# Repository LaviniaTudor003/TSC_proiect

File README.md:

# e-book reader

# BOM (Bill Of Materials)

| Component                       | Supplier Link | Datasheet |
|--------------------------------|----------------|-----------|
| 744043680                     | [Model](https://ro.mouser.com/ProductDetail/Wurth-Elektronik/744043680?qs=PGXP4M47uW6VkZq%252BkzjrHA%3D%3D)   | [Datasheet](https://www.we-online.com/components/products/datasheet/744043680.pdf) |
| BD5229G-TR                    | [Model](https://www.digikey.ee/en/models/658502) | [Datasheet](https://www.rohm.com/datasheet?p=BD5229G&dist=Digi-key&media=referral&source=digi-key.com&campaign=Digi-key) |
| Capacitor 0402               | [Model](https://componentsearchengine.com/part-view/CC0402MRX5R5BB106/YAGEO) | [Datasheet](https://componentsearchengine.com/Datasheets/2/CC0402MRX5R5BB106.pdf) |
| CPH3225A                      | [Model](https://www.snapeda.com/parts/CPH3225A/Seiko+Instruments/view-part/?ref=eda)   | [Datasheet](https://www.snapeda.com/parts/CPH3225A/Seiko%20Instruments/datasheet/) |
| Custom Button                 | [Model](https://industry.panasonic.com/global/en/products/control/switch/light-touch/number/evqpuj02k) | [Datasheet](https://industry.panasonic.com/global/en/downloads?tab=catalog&small_g_cd=203&part_no=EVQPUJ02K) |
| MBR0530 Schottky Diode       | [Model](https://www.snapeda.com/parts/MBR0530/Onsemi/view-part/?ref=eda)                | [Datasheet](https://www.snapeda.com/parts/MBR0530/ON%20Semiconductor/datasheet/) |
| PGB1010603MR                 | [Model](https://www.snapeda.com/parts/PGB1010603MR/Littelfuse/view-part/?ref=eda)                | [Datasheet](https://www.snapeda.com/parts/PGB1010603MR/Littelfuse%20Inc./datasheet/) |
| QWIIC Connector              | [Model](https://www.snapeda.com/parts/PRT-14417/SparkFun/view-part/)                | [Datasheet](https://www.snapeda.com/parts/PRT-14417/SparkFun%20Electronics/datasheet/) |
| USB4110-GF-A                 | [Model](https://componentsearchengine.com/part-view/USB4110-GF-A/GCT%20(GLOBAL%20CONNECTOR%20TECHNOLOGY))                | [Datasheet](https://gct.co/files/drawings/usb4110.pdf) |
| USBLC6-2SC6Y                 | [Model](https://www.snapeda.com/parts/USBLC6-2SC6Y/STMicroelectronics/view-part/?ref=eda) | [Datasheet](https://www.snapeda.com/parts/USBLC6-2SC6Y/STMicroelectronics/datasheet/) |
| W25Q512JVEIQ                | [Model](https://www.digikey.ro/en/models/10244706)             | [Datasheet](https://www.winbond.com/resource-files/W25Q512JV%20SPI%20RevB%2006252019%20KMS.pdf) |
| RCL CPOL 3528                | [Model](https://www.snapeda.com/parts/TAJB475K025RNJ/AVX/view-part/?ref=dk&t=capacitor%203528&con_ref=None)                | [Datasheet](https://s3.amazonaws.com/snapeda/datasheet/TAJB475K025RNJ_AVX.pdf) |
| DS3231SN                      | [Model](https://www.snapeda.com/parts/DS3231SN%23/Analog+Devices/view-part/?ref=eda) | [Datasheet](https://www.snapeda.com/parts/DS3231SN%23/Analog%20Devices/datasheet/) |
| ESP32 WROVER 0805 Capacitor  | [Model](https://ro.mouser.com/ProductDetail/KYOCERA-AVX/SD0805S020S1R0?qs=jCA%252BPfw4LHbpkAoSnwrdjw%3D%3D)                | [Datasheet](https://ro.mouser.com/datasheet/2/40/schottky-3165252.pdf) |
| ESP32 WROVER BME680 Sensor   | [Model](https://www.digikey.ro/en/models/7401317)                | [Datasheet](https://www.bosch-sensortec.com/media/boschsensortec/downloads/datasheets/bst-bme680-ds001.pdf) |
| ESP32 WROVER MCP73831 Power Management | [Model](https://www.snapeda.com/parts/MCP73831T-2ACI/OT/Microchip/view-part/)         | [Datasheet](https://www.snapeda.com/parts/MCP73831T-2ACI/OT/Microchip/datasheet/) |
| ESP32C6 Varistor 1812        | [Model](https://www.snapeda.com/parts/RC0603JR-070RL/Yageo/view-part/)                | [Datasheet](https://www.snapeda.com/parts/RC0603JR-070RL/Yageo/datasheet/) |
| ESP32C6 WROOM-1-N8           | [Model](https://www.snapeda.com/parts/ESP32-C6-WROOM-1-N8/Espressif+Systems/view-part/?ref=eda)                | [Datasheet](https://www.snapeda.com/parts/ESP32-C6-WROOM-1-N8/Espressif%20Systems/datasheet/) |
| FH34SRJ-24S-0.5SH            | [Model](https://www.snapeda.com/parts/FH34SRJ-24S-0.5SH(99)/Hirose/view-part/)                | [Datasheet](https://www.snapeda.com/parts/FH34SRJ-24S-0.5SH(99)/Hirose%20Connector/datasheet/) |
| LED Chip 0603                | [Model](https://grabcad.com/library/0603-smd-led-1)                | [Datasheet](https://www.snapeda.com/parts/KP-1608SURCK/Kingbright/datasheet/) |
| MAX17048G+T10                | [Model](https://www.snapeda.com/parts/MAX17048G+T10/Analog+Devices/view-part/?ref=eda)                | [Datasheet](https://www.snapeda.com/parts/MAX17048G+T10/Analog%20Devices/datasheet/) |
| Resistor 0402                | [Model](https://componentsearchengine.com/part-view/R0402%201%25%20100%20K%20(RC0402FR-07100KL)/YAGEO)                | [Datasheet](https://www.yageo.com/upload/media/product/products/datasheet/rchip/PYu-RC_Group_51_RoHS_L_12.pdf) |
| 112A-TAAR-R03                  | [Model](https://www.snapeda.com/parts/112A-TAAR-R03/Attend/view-part/) | [Datasheet](https://www.snapeda.com/parts/112A-TAAR-R03/Attend/datasheet/) |
| SI1308EDL-T1-GE3 MOSFET      | [Model](https://www.snapeda.com/parts/SI1308EDL-T1-GE3/Vishay+Siliconix/view-part/?ref=eda)                | [Datasheet](https://www.snapeda.com/parts/SI1308EDL-T1-GE3/Vishay%20Siliconix/datasheet/) |
| SJ                           | [Model](https://grabcad.com/library/solder-jumpers-1)                | [Datasheet](https://github.com/TeodorStamatin/EBook_Reader/tree/main) |
| XC6220A331MR-G              | [Model](https://componentsearchengine.com/part-view/XC6220A331MR-G/Torex)             | [Datasheet](https://product.torexsemi.com/system/files/series/xc6220.pdf) |

# Conexiuni și module hardware utilizate:
•	USB-C Connector + ESD Protection
-	Intrare principală de alimentare și programare.
•	LDO Voltage Regulator
-	Reglează tensiunea de intrare la 3.3V stabil pentru alimentarea ESP32 și altor componente.
•	Li-Po Battery Charging Controller
-	Încarcă un acumulator Li-Po de la 5V (USB)
•	ESP32-C6
-	Microcontroller principal - responsabil de control, procesare si comunicare
•	E-Paper Drive Circuit
-	Oferă semnalul de putere necesar pentru activarea e-paper-ului
•	Display Type Selector
-	Permite comutarea
•	Voltage Supervisor + Reset
-	Asigură resetul corect la pornire
Poziționarea componentelor a fost gândită pentru:
•	acces facil la butoane,
•	vizibilitatea e-paper-ului,
•	montarea sigură a bateriei cu suport mecanic.
(pe baza schemei si recomandarilor primite)

# Functionalitate Hardware:
**Componente, Module și Senzori**
**Alimentare și Management Energie**
 Conector USB-C + Protecție ESD
 Funcție: Asigură alimentarea principală a sistemului și protejează împotriva descărcărilor electrostatice.
 
 Controler Încărcare Baterie – MCP73831
 Funcție: Gestionează încărcarea bateriei Li-Po, controlează curentul de încărcare.
 
 Baterie Li-Po
 Funcție: Sursă de alimentare secundară pentru funcționare autonomă (fără USB).
 
 Regulator de Tensiune LDO (3.3V)
 Funcție: Stabilizează tensiunea de alimentare pentru microcontroler și restul componentelor.
 
 Supervizor Tensiune + Buton Reset/Boot
 Funcție: Monitorizează nivelul tensiunii de alimentare și permite resetarea sau intrarea în modul boot al ESP32-C6.

**Control și Procesare:**
 ESP32-C6-WROOM-1-N8
 Funcție: Microcontroler principal. Gestionează comunicațiile (SPI, I2C, UART), interacțiunea cu senzorii și controlul perifericelor. Oferă conectivitate Wi-Fi și Bluetooth Low Energy.
 
 Memorie Externă NOR Flash – 64MB
 Funcție: Stocare extinsă pentru firmware și date.
 Interfață: SPI.

**Timp Real:**
 Modul RTC – DS3231SN
 Funcție: Ceas de timp real de înaltă precizie, cu suport pentru alarmă și funcționare pe baterie de backup.
 Interfață: I2C.

**Senzori de Mediu:**
 BME688 – Senzor ambiental
 Funcție: Măsoară temperatura, umiditatea, presiunea atmosferică și compușii organici volatili (VOC).
 Interfață: I2C (Qwiic / Stemma QT pentru conectare rapidă).
 Consum: Standby ultra-low power, activ ~3.1 mA.

**Afișaj:**
 Circuit de control pentru ecran E-Paper + Header de conectare
 Funcție: Generează semnalele necesare pentru funcționarea ecranelor E-Paper.
 Interfață: SPI cu linii de control dedicate (Busy, Reset, DC, CS).

**Stocare locală:**
 Slot Card microSD
 Funcție: Permite salvarea datelor local (loguri, configurări, fișiere).
 Interfață: SPI, cu semnal Chip Select dedicat.

**Interfețe de Comunicație:**
 I2C: Utilizat pentru BME688 și DS3231SN.
 SPI: Utilizat pentru NOR Flash, E-Paper Display și Card SD.
 UART: Disponibil pentru debug sau extensii opționale.
 Wi-Fi & Bluetooth LE: Oferite de modulul ESP32-C6.
# Pini ESP32-C6

| Componenta / Rol                             | Pin ESP32-C6     | Motivație                                           |
|---------------------------------------------|------------------|-----------------------------------------------------|
| I2C SDA către BME688 și DS3231SN             | IO14 (SDA)       | Transmite date între microcontroler și dispozitivele I2C. |
| I2C SCL către BME688 și DS3231SN             | IO15 (SCL)       | Coordonează sincronizarea comunicării I2C.          |
| SPI MOSI către NOR Flash, E-Paper, SD Card   | IO6 (MOSI)       | Trimite informații din ESP32 către perifericele conectate pe SPI. |
| SPI MISO din NOR Flash, E-Paper, SD Card     | IO7 (MISO)       | Primește date înapoi de la dispozitivele SPI.       |
| SPI Clock                                     | IO8 (SCK)        | Oferă impulsurile de sincronizare pentru magistrala SPI. |
| Chip Select NOR Flash                         | IO9 (CS1)        | Activează memoria NOR atunci când este utilizată.   |
| Chip Select E-Paper Display                   | IO10 (CS2)       | Selectează modulul de afișaj E-Paper pentru transmiterea de date. |
| Chip Select SD Card                           | IO11 (CS3)       | Indică faptul că SD Card-ul este dispozitivul activ pe SPI. |
| UART RX, TX (debug)                           | IO16, IO17       | Permite trimiterea și recepționarea datelor pentru depanare și upload firmware. |
| Reset / Boot control                          | IO21             | Folosit pentru repornirea manuală a sistemului sau inițierea modului de programare. |

# PCB_2D:

# PCB_3D:

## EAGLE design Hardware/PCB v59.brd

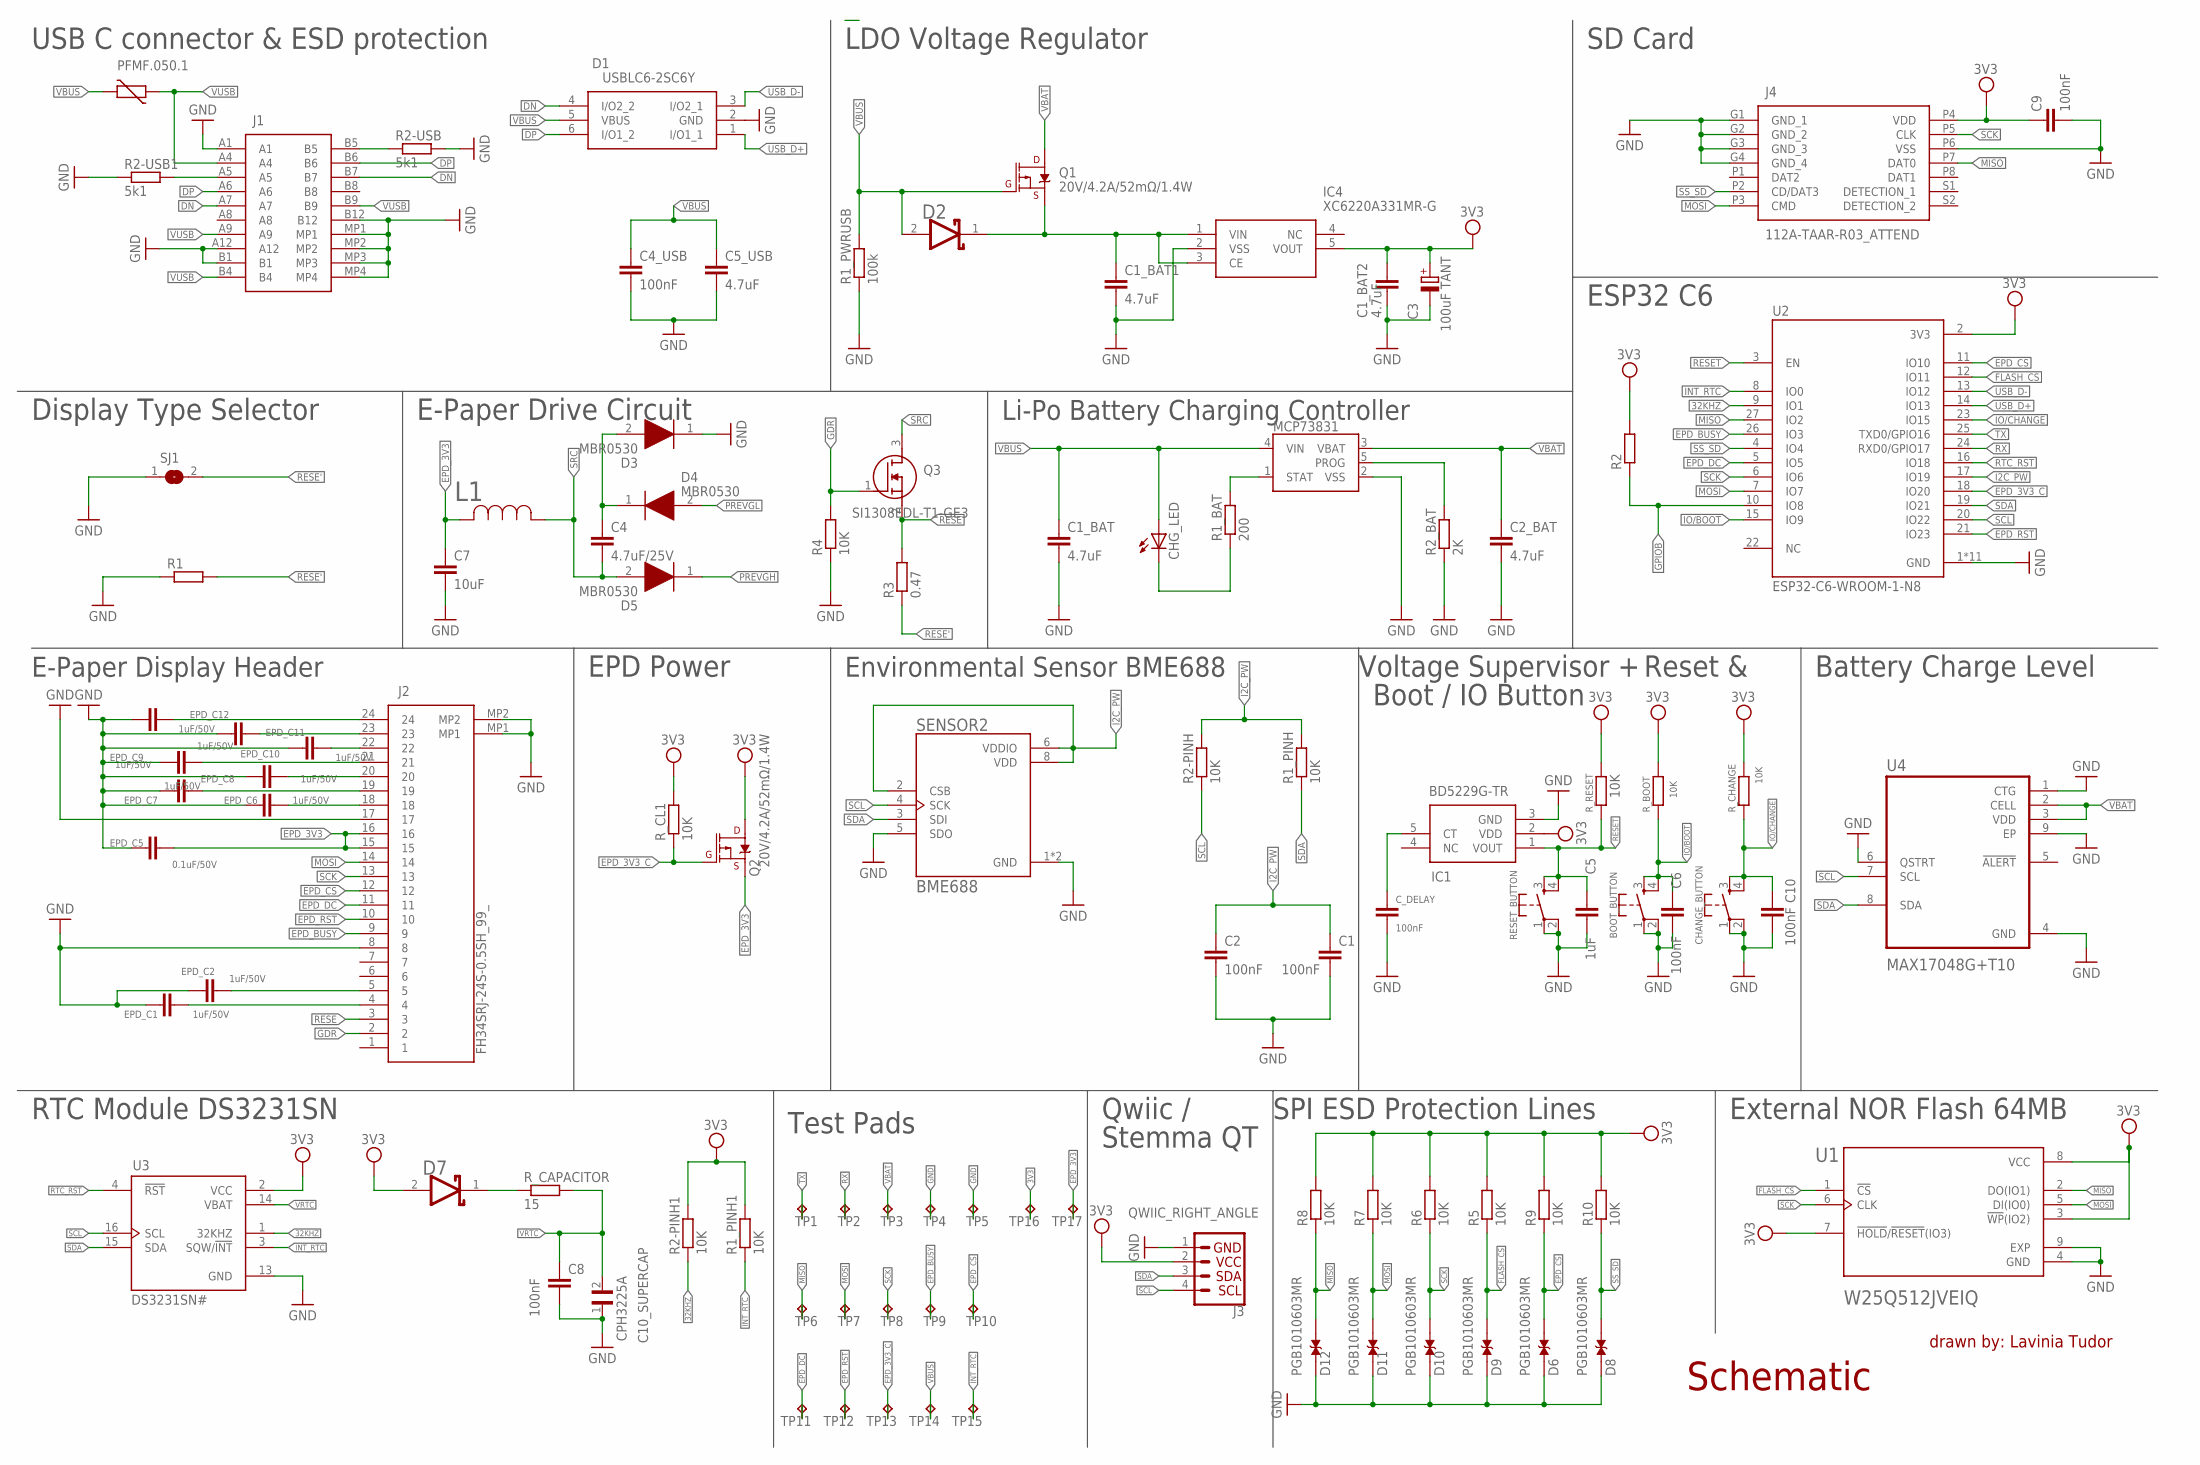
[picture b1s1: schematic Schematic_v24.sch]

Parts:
BOOT_BUTTON: BUTTON_CUSYOMV1; MYBUTTON
C1, C2, C6, C8, C10: 100nF; ESP32_WROVER_EAGLE-LTSPICE_C0402
C1_BAT, C1_BAT1, C1_BAT2, C2_BAT: 4.7uF; ESP32_WROVER_EAGLE-LTSPICE_C0402
C3: 100uF TANT; RCL_CT3528
C4: 4.7uF/25V; ESP32_WROVER_EAGLE-LTSPICE_C0402
C4_USB, C9: 100nF; EAGLE-LTSPICE_C0402
C5: 1uF; ESP32_WROVER_EAGLE-LTSPICE_C0402
C5_USB: 4.7uF; EAGLE-LTSPICE_C0402
C7: 10uF; ESP32_WROVER_EAGLE-LTSPICE_C0402
C10_SUPERCAP: CPH3225A; CAPCP3225X100N
CHANGE_BUTTON: BUTTON_CUSYOMV1; MYBUTTON
CHG_LED: ADAFRUIT_LEDCHIP-LED0603; ADAFRUIT_CHIP-LED0603
C_DELAY: 100nF; ESP32_WROVER_EAGLE-LTSPICE_C0402
D1: USBLC6-2SC6Y; SOT95P280X145-6N
D2, D7: ESP32_WROVER_AVX---SD0805S020S1R0_AVX_SD0805S020S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; ESP32_WROVER_AVX---SD0805S020S1R0_AVX_SD0805S020S1R0_0
D3, D4, D5: MBR0530; SOD3716X135N
D6, D8, D9, D10, D11, D12: PGB1010603MR; DIOC1608X36N
EPD_C1, EPD_C2, EPD_C6, EPD_C7, EPD_C8, EPD_C9, EPD_C10, EPD_C11, EPD_C12: 1uF/50V; ESP32_WROVER_EAGLE-LTSPICE_C0402
EPD_C5: 0.1uF/50V; ESP32_WROVER_EAGLE-LTSPICE_C0402
IC1: BD5229G-TR; SOT95P280X125-5N
IC4: XC6220A331MR-G; SOT95P280X120-5N
J1: SAMACSYS_PARTS_USB4110-GF-A; SAMACSYS_PARTS_USB4110GFA
J2: FH34SRJ-24S-0.5SH_99_; FH34SRJ24S05SH99
J3: QWIIC_RIGHT_ANGLE; JST04_1MM_RA
J4: 112A-TAAR-R03_ATTEND; 112ATAARR03ATTEND
L1: 744043680IND_4828-WE-TPC_WRE; IND_4828-WE-TPC_WRE
MCP73831: ESP32_WROVER_SPARKFUN-IC-POWER_MCP73831; ESP32_WROVER_SPARKFUN-IC-POWER_SOT23-5
PFMF.050.1: ESP32C6_VARISTORCN1812; ESP32C6_VARISTOR_CT/CN1812
Q1, Q2: 20V/4.2A/52mΩ/1.4W; ESP32_WROVER_SPARKFUN-DISCRETESEMI_SOT23-3
Q3: SI1308EDL-T1-GE3; SOT65P210X110-3N
R1, R2: ESP32_WROVER_EAGLE-LTSPICE_RR0402; ESP32_WROVER_EAGLE-LTSPICE_R0402
R1_BAT: 200; ESP32_WROVER_EAGLE-LTSPICE_R0402
R1_PINH, R1_PINH1, R2-PINH, R2-PINH1, R4, R5, R6, R7, R8, R9, R10: 10K; ESP32_WROVER_EAGLE-LTSPICE_R0402
R1_PWRUSB: 100k; ESP32_WROVER_EAGLE-LTSPICE_R0402
R2-USB, R2-USB1: 5k1; ESP32_WROVER_EAGLE-LTSPICE_R0402
R2_BAT: 2K; ESP32_WROVER_EAGLE-LTSPICE_R0402
R3: 0.47; ESP32_WROVER_EAGLE-LTSPICE_R0402
RESET_BUTTON: BUTTON_CUSYOMV1; MYBUTTON
R_BOOT: 10K; ESP32_WROVER_EAGLE-LTSPICE_R0402
R_CAPACITOR: 15; ESP32_WROVER_EAGLE-LTSPICE_R0402
R_CHANGE: 10K; ESP32_WROVER_EAGLE-LTSPICE_R0402
R_CL1: 10K; ESP32_WROVER_EAGLE-LTSPICE_R0402
R_RESET: 10K; ESP32_WROVER_EAGLE-LTSPICE_R0402
SENSOR2: BME688; ESP32_WROVER_BME680_PSON80P300X300X100-8N
SJ1: SJ
TP1, TP2, TP3, TP4, TP5, TP6, TP7, TP8, TP9, TP10, TP11, TP12, TP13, TP14, TP15, TP16, TP17: TPTP20R; TP20R
U1: W25Q512JVEIQ; SON127P600X800X80-9N
U2: ESP32-C6-WROOM-1-N8; XCVR_ESP32-C6-WROOM-1-N8
U3: DS3231SN#; SOIC127P1032X265-16N
U4: MAX17048G+T10; SON50P200X200X80-9N

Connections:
3V3: C1_BAT2.1, C3.+, C9.1, D7.2 (ANODE), IC1.2 (VDD), IC4.5 (VOUT), J3.2, J4.P4 (VDD), Q2.3 (D), R1_PINH1.2, R2.2, R2-PINH1.2, R5.2, R6.2, R7.2, R8.2, R9.2, R10.2, R_BOOT.2, R_CHANGE.2, R_CL1.2, R_RESET.2, TP16.TP, U1.3 (!WP!(IO2)), U1.7 (!HOLD!/!RESET!(IO3)), U1.8 (VCC), U2.2 (3V3), U3.2 (VCC)
32KHZ: R2-PINH1.1, U2.9 (IO1), U3.1 (32KHZ)
DN: D1.4 (I/O2_2), J1.A7, J1.B7
DP: D1.6 (I/O1_2), J1.A6, J1.B6
EPD_3V3: C7.1, EPD_C5.2, J2.15, J2.16, L1.2, Q2.2 (S), TP17.TP
EPD_3V3_C: Q2.1 (G), R_CL1.1, TP13.TP, U2.18 (IO20)
EPD_BUSY: J2.9, TP9.TP, U2.26 (IO3)
EPD_CS: D6.2, J2.12, R9.1, TP10.TP, U2.11 (IO10)
EPD_DC: J2.11, TP11.TP, U2.5 (IO5)
EPD_RST: J2.10, TP12.TP, U2.21 (IO23)
FLASH_CS: D9.2, R5.1, U1.1 (!CS), U2.12 (IO11)
GDR: J2.2, Q3.1 (G), R4.2
GND: BOOT_BUTTON.1, BOOT_BUTTON.2, C1.2, C1_BAT.2, C1_BAT1.2, C1_BAT2.2, C2.2, C2_BAT.2, C3.-, C4_USB.2, C5.2, C5_USB.2, C6.2, C7.2, C8.2, C9.2, C10.2, C10_SUPERCAP.1, CHANGE_BUTTON.1, CHANGE_BUTTON.2, C_DELAY.2, D1.2 (GND), D3.1 (K), D6.1, D8.1, D9.1, D10.1, D11.1, D12.1, EPD_C1.1, EPD_C2.1, EPD_C5.1, EPD_C6.1, EPD_C7.1, EPD_C8.1, EPD_C9.1, EPD_C10.1, EPD_C11.1, EPD_C12.1, IC1.3 (GND), IC4.2 (VSS), J1.A1, J1.A12, J1.B1, J1.B12, J1.MP1, J1.MP2, J1.MP3, J1.MP4, J2.8, J2.17, J2.MP1, J2.MP2, J3.1, J4.G1 (GND_1), J4.G2 (GND_2), J4.G3 (GND_3), J4.G4 (GND_4), J4.P6 (VSS), MCP73831.2 (VSS), R1.1, R1_PWRUSB.1, R2-USB.2, R2-USB1.1, R2_BAT.1, R4.1, RESET_BUTTON.1, RESET_BUTTON.2, SENSOR2.1 (GND), SENSOR2.5 (SDO), SENSOR2.7 (GND), SJ1.1, TP4.TP, TP5.TP, U1.4 (GND), U1.9 (EXP), U2.1 (GND), U2.28 (GND), U2.29_1 (GND), U2.29_2 (GND), U2.29_3 (GND), U2.29_4 (GND), U2.29_5 (GND), U2.29_6 (GND), U2.29_7 (GND), U2.29_8 (GND), U2.29_9 (GND), U3.13 (GND), U4.1 (CTG), U4.4 (GND), U4.6 (QSTRT), U4.9 (EP)
GPIOB: R2.1, U2.10 (IO8)
I2C_PW: C1.1, C2.1, R1_PINH.2, R2-PINH.2, SENSOR2.2 (CSB), SENSOR2.6 (VDDIO), SENSOR2.8 (VDD), U2.17 (IO19)
INT_RTC: R1_PINH1.1, TP15.TP, U2.8 (IO0), U3.3 (SQW/!INT)
IO/BOOT: BOOT_BUTTON.3, BOOT_BUTTON.4, C6.1, R_BOOT.1, U2.15 (IO9)
IO/CHANGE: C10.1, CHANGE_BUTTON.3, CHANGE_BUTTON.4, R_CHANGE.1, U2.23 (IO15)
MISO: D12.2, J4.P7 (DAT0), R8.1, TP6.TP, U1.2 (DO(IO1)), U2.27 (IO2)
MOSI: D11.2, J2.14, J4.P3 (CMD), R7.1, TP7.TP, U1.5 (DI(IO0)), U2.7 (IO7)
unnamed: C1_BAT1.1, D2.1 (CATHODE), IC4.1 (VIN), IC4.3 (CE), Q1.2 (S)
unnamed: J1.A5, R2-USB1.2
unnamed: J1.B5, R2-USB.1
unnamed: C4.1, D3.2 (A), D4.1 (K)
unnamed: EPD_C12.2, J2.24
unnamed: CHG_LED.C, R1_BAT.1
unnamed: MCP73831.1 (STAT), R1_BAT.2
unnamed: MCP73831.5 (PROG), R2_BAT.2
unnamed: EPD_C11.2, J2.23
unnamed: EPD_C10.2, J2.22
unnamed: EPD_C9.2, J2.21
unnamed: EPD_C8.2, J2.20
unnamed: EPD_C7.2, J2.19
unnamed: EPD_C6.2, J2.18
unnamed: C_DELAY.1, IC1.5 (CT)
unnamed: EPD_C2.2, J2.5
unnamed: D7.1 (CATHODE), R_CAPACITOR.1
unnamed: EPD_C1.2, J2.4
PREVGH: D5.1 (K)
PREVGL: D4.2 (A)
RESE: J2.3, Q3.2 (S), R3.2
RESE': R1.2, R3.1, SJ1.2
RESET: C5.1, IC1.1 (VOUT), RESET_BUTTON.3, RESET_BUTTON.4, R_RESET.1, U2.3 (EN)
RTC_RST: U2.16 (IO18), U3.4 (!RST)
RX: TP2.TP, U2.24 (RXD0/GPIO17)
SCK: D10.2, J2.13, J4.P5 (CLK), R6.1, TP8.TP, U1.6 (CLK), U2.6 (IO6)
SCL: J3.4, R2-PINH.1, SENSOR2.4 (SCK), U2.20 (IO22), U3.16 (SCL), U4.7 (SCL)
SDA: J3.3, R1_PINH.1, SENSOR2.3 (SDI), U2.19 (IO21), U3.15 (SDA), U4.8 (SDA)
SRC: C4.2, D5.2 (A), L1.1, Q3.3 (D)
SS_SD: D8.2, J4.P2 (CD/DAT3), R10.1, U2.4 (IO4)
TX: TP1.TP, U2.25 (TXD0/GPIO16)
USB_D+: D1.1 (I/O1_1), U2.14 (IO13)
USB_D-: D1.3 (I/O2_1), U2.13 (IO12)
VBAT: C2_BAT.1, MCP73831.3 (VBAT), Q1.3 (D), TP3.TP, U4.2 (CELL), U4.3 (VDD)
VBUS: C1_BAT.1, C4_USB.1, C5_USB.1, CHG_LED.A, D1.5 (VBUS), D2.2 (ANODE), MCP73831.4 (VIN), PFMF.050.1.2, Q1.1 (G), R1_PWRUSB.2, TP14.TP
VRTC: C8.1, C10_SUPERCAP.2, R_CAPACITOR.2, U3.14 (VBAT)
VUSB: J1.A4, J1.A9, J1.B4, J1.B9, PFMF.050.1.1

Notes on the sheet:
drawn by: Lavinia Tudor
Schematic
USB C connector & ESD protection
LDO Voltage Regulator
Display Type Selector
E-Paper Drive Circuit
SD Card
ESP32 C6
Battery Charge Level
Voltage Supervisor +
Reset &
Boot / IO Button
Environmental Sensor BME688
EPD Power
E-Paper Display Header
Li-Po Battery Charging Controller
RTC Module DS3231SN
Test Pads
Qwiic /
Stemma QT
SPI ESD Protection Lines
External NOR Flash 64MB

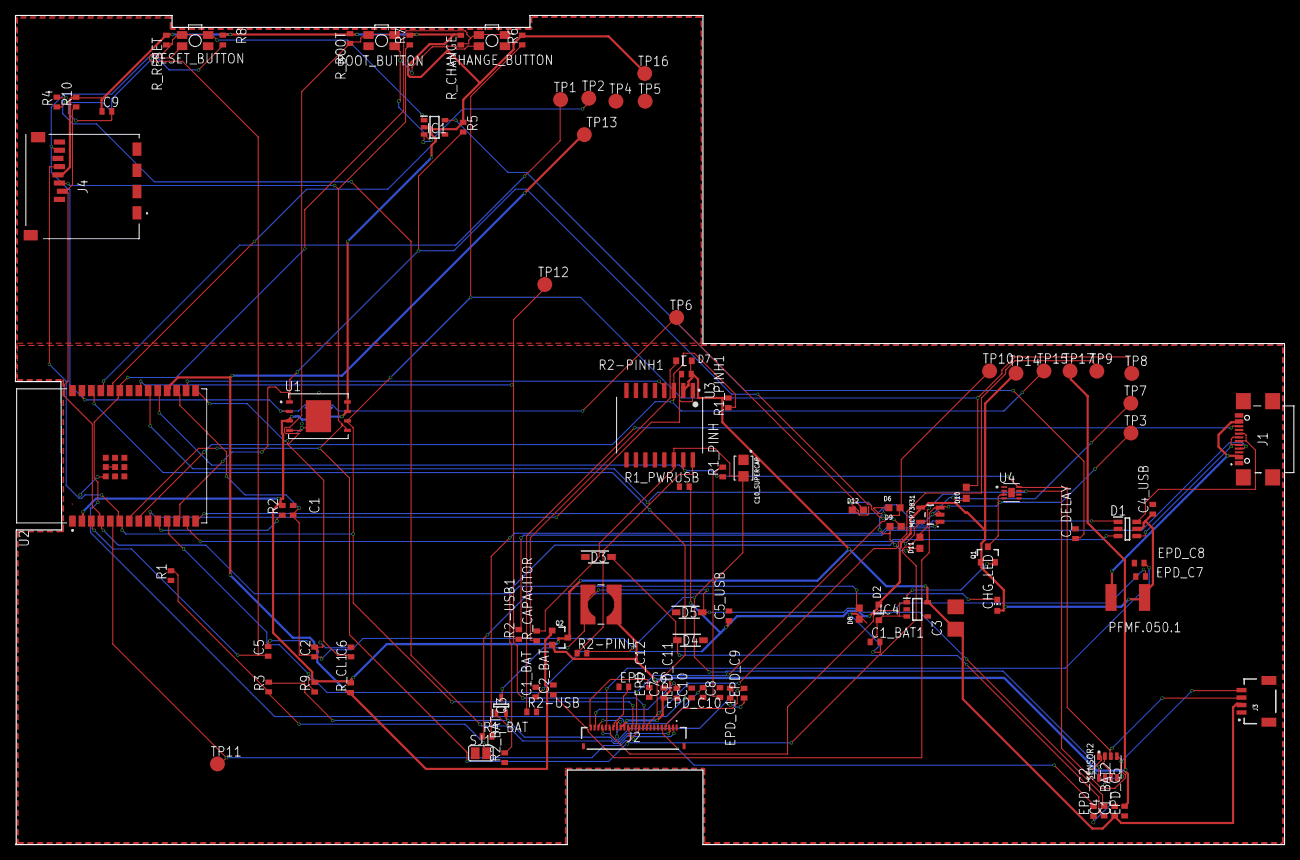
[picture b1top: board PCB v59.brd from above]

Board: 2 copper layers, 170.2 x 111.2 mm, 103 parts (0 on the bottom side), 55 nets.

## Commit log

2025-03-30 Am terminat schematicul
2025-03-31 Am facut niste modificari
2025-03-31 Am reparat eroarea din Schematic
2025-04-06 BOARD_PCB
2025-04-06 varianta pcb_25 de fire galbene ramase
2025-04-06 au mai ramas 13 erori la pcb
2025-04-06 Am sters duplicatele
2025-04-06 Gata cu pcb-ul
2025-04-06 Am exportat fisierele Gerber si Assembly
2025-04-06 Am creat structura ptr git ca in enunt
2025-04-06 Ne apropiem de final
2025-04-06 Create LICENSE
2025-04-12 issue1 - rezolvat
2025-04-13 Schematic salvat in forma .sch si pcb cu reparatiile facute sub forma .brd
2025-04-14 Gata modelul 3D
2025-04-14 Am adaugat .step
2025-04-14 Manufacturing - reparat
2025-04-14 Manufacturing - reparat - am schimbat numele
2025-04-14 Imagini - update

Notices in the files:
parts and their libraries:
COPYRIGHT: Copyright (C) 2024 Ultra Librarian. All rights reserved.
